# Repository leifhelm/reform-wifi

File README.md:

# WiFi Adapter for MNT Reform

This module is **untested**.

This adapter uses the PCIe and USB interfaces of the RCORE module, like the Pocket Reform.

The schematic is largely from [pocket-reform-wifi](https://source.mnt.re/reform/pocket-reform/-/tree/2fd691b93a8a8b05e923d17600f8ea777f0ab824/pocket-reform-wifi).

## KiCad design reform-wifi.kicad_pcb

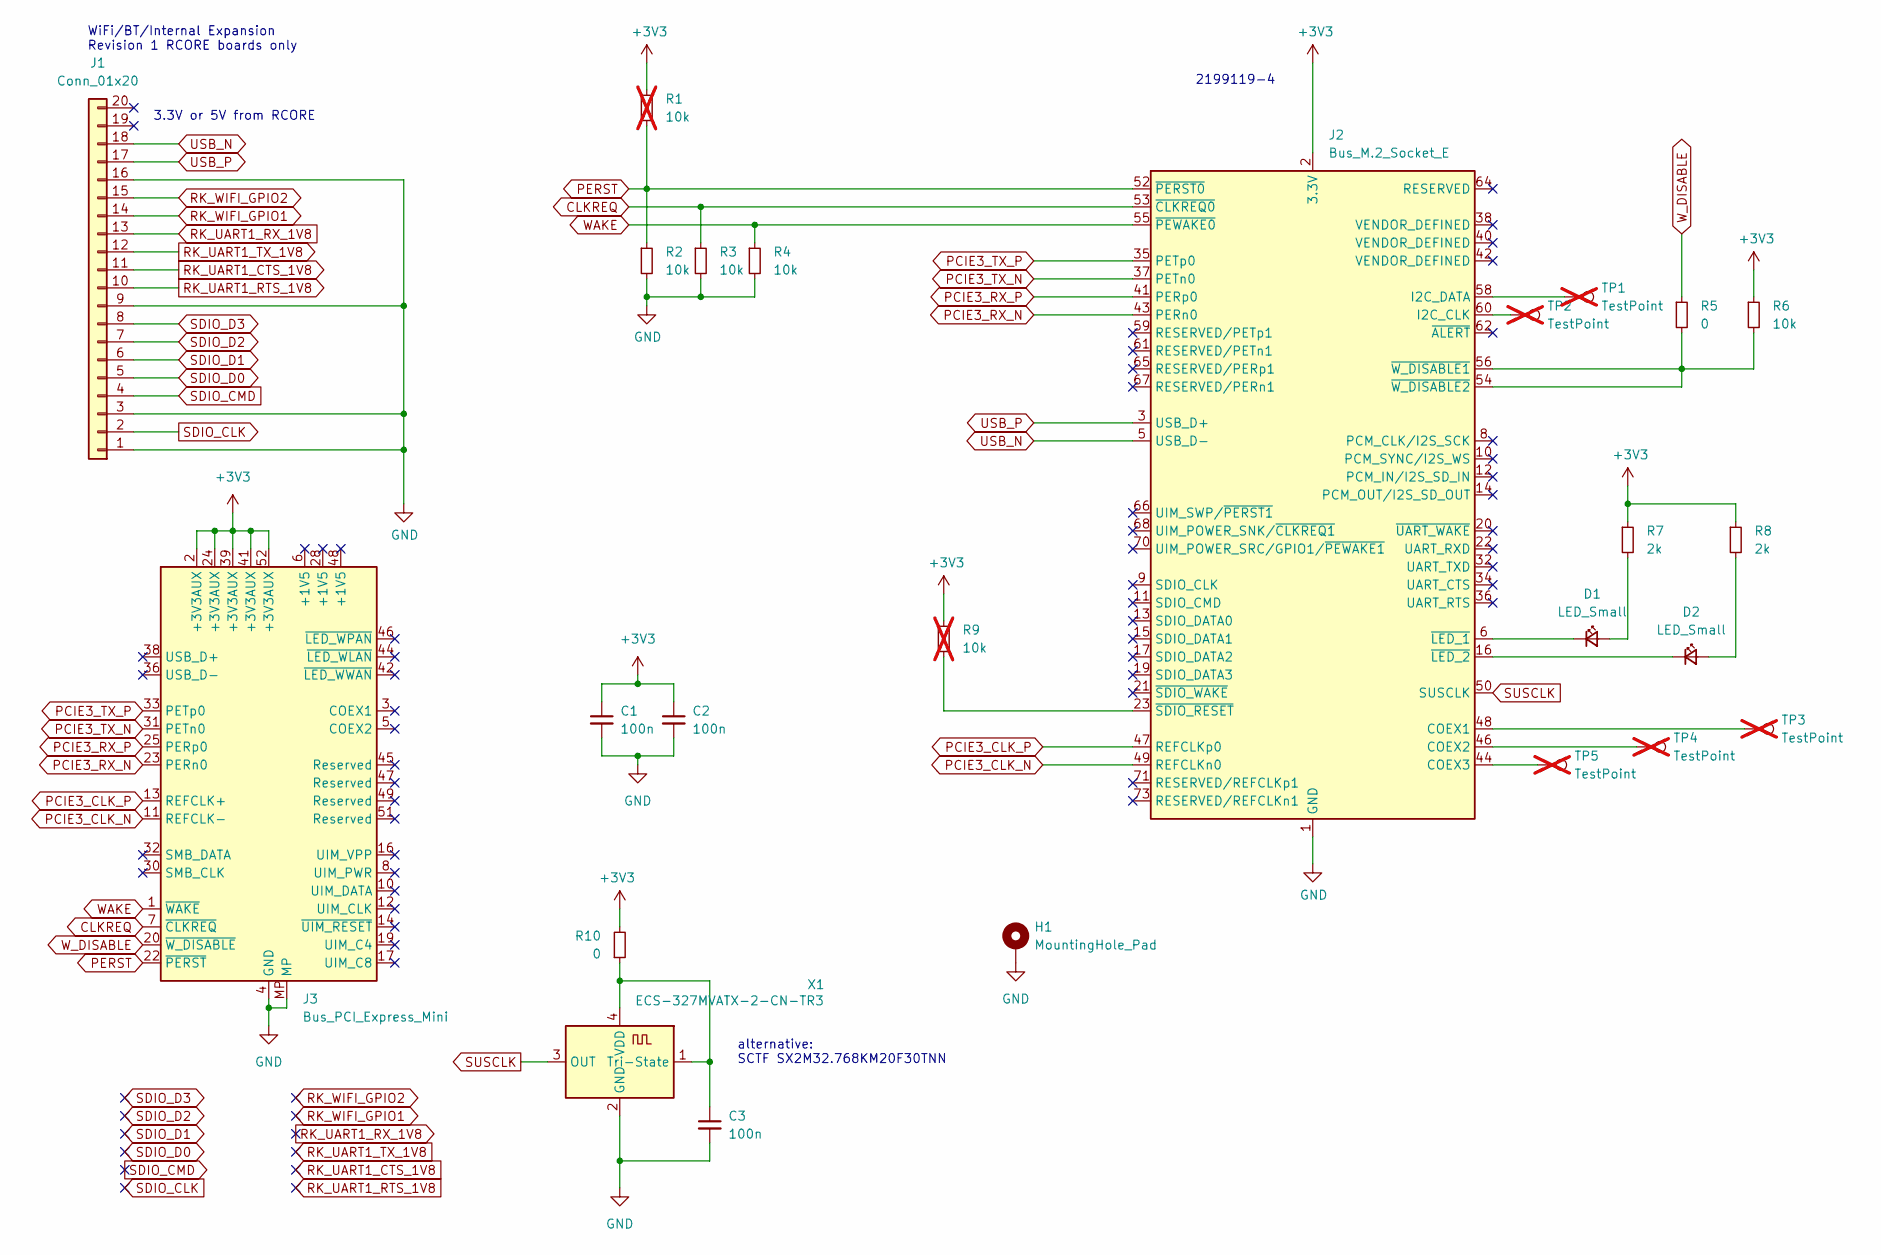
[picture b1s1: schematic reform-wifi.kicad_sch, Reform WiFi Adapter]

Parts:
C1, C2, C3: 100n; C_0603_1608Metric; LCSC C77058
D1, D2: LED_Small; LED_0603_1608Metric; LCSC C5875723
H1: MountingHole_Pad; M.2 Mounting; LCSC C2916320
J1: Conn_01x20; Hirose_FH12-20S-0.5SH_1x20-1MP_P0.50mm_Horizontal; LCSC C596730
J2: Bus_M.2_Socket_E; TE_2199119-4; LCSC C5163551
J3: Bus_PCI_Express_Mini; BUS_PCI_Express_Mini_Full_Card
R1, R9: 10k; R_0603_1608Metric; LCSC C98220; not fitted
R2, R3, R4, R6: 10k; R_0603_1608Metric; LCSC C98220
R5, R10: 0; R_0603_1608Metric; LCSC C95177
R7, R8: 2k; R_0603_1608Metric; LCSC C105576
TP1, TP2, TP3, TP4, TP5: TestPoint; TestPoint_Pad_D1.0mm; not fitted
X1: ECS-327MVATX-2-CN-TR3; Oscillator_SMD_ECS_2520MV-xxx-xx-4Pin_2.5x2.0mm; LCSC C2901603

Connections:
+3V3: C1.1, C2.1, J2.2 (3.3V), J2.4 (3.3V), J2.72 (3.3V), J2.74 (3.3V), J3.2 (+3V3AUX), J3.24 (+3V3AUX), J3.39 (+3V3AUX), J3.41 (+3V3AUX), J3.52 (+3V3AUX), R1.1, R6.1, R7.1, R8.1, R9.1, R10.2
CLKREQ: J2.53 (~CLKREQ0), J3.7 (~CLKREQ), R3.1
GND: C1.2, C2.2, C3.2, H1.1, J1.1, J1.3, J1.9, J1.16, J2.1 (GND), J2.7 (GND), J2.18 (GND), J2.33 (GND), J2.39 (GND), J2.45 (GND), J2.51 (GND), J2.57 (GND), J2.63 (GND), J2.69 (GND), J2.75 (GND), J3.4 (GND), J3.9 (GND), J3.15 (GND), J3.18 (GND), J3.21 (GND), J3.26 (GND), J3.27 (GND), J3.29 (GND), J3.34 (GND), J3.35 (GND), J3.37 (GND), J3.40 (GND), J3.43 (GND), J3.50 (GND), J3.MP, R2.2, R3.2, R4.2, X1.2 (GND)
unnamed: D1.2 (A), R7.2
unnamed: D1.1 (K), J2.6 (~LED_1)
unnamed: D2.2 (A), R8.2
unnamed: D2.1 (K), J2.16 (~LED_2)
unnamed: J2.48 (COEX1), TP3.1
unnamed: J2.46 (COEX2), TP4.1
unnamed: J2.44 (COEX3), TP5.1
unnamed: J2.60 (I2C_CLK), TP2.1
unnamed: J2.58 (I2C_DATA), TP1.1
unnamed: J2.23 (~SDIO_RESET), R9.2
unnamed: J2.54 (~W_DISABLE2), J2.56 (~W_DISABLE1), R5.2, R6.2
unnamed: C3.1, R10.1, X1.1 (Tri-State), X1.4 (VDD)
PCIE3_CLK_N: J2.49 (REFCLKn0), J3.11 (REFCLK-)
PCIE3_CLK_P: J2.47 (REFCLKp0), J3.13 (REFCLK+)
PCIE3_RX_N: J2.43 (PERn0), J3.23 (PERn0)
PCIE3_RX_P: J2.41 (PERp0), J3.25 (PERp0)
PCIE3_TX_N: J2.37 (PETn0), J3.31 (PETn0)
PCIE3_TX_P: J2.35 (PETp0), J3.33 (PETp0)
PERST: J2.52 (~PERST0), J3.22 (~PERST), R1.2, R2.1
RK_UART1_CTS_1V8: J1.11
RK_UART1_RTS_1V8: J1.10
RK_UART1_RX_1V8: J1.13
RK_UART1_TX_1V8: J1.12
RK_WIFI_GPIO1: J1.14
RK_WIFI_GPIO2: J1.15
SDIO_CLK: J1.2
SDIO_CMD: J1.4
SDIO_D0: J1.5
SDIO_D1: J1.6
SDIO_D2: J1.7
SDIO_D3: J1.8
SUSCLK: J2.50 (SUSCLK), X1.3 (OUT)
USB_N: J1.18, J2.5 (USB_D-)
USB_P: J1.17, J2.3 (USB_D+)
WAKE: J2.55 (~PEWAKE0), J3.1 (~WAKE), R4.1
W_DISABLE: J3.20 (~W_DISABLE), R5.1

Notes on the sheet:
2199119-4
alternative: SCTF SX2M32.768KM20F30TNN
3.3V or 5V from RCORE
WiFi/BT/Internal Expansion Revision 1 RCORE boards only

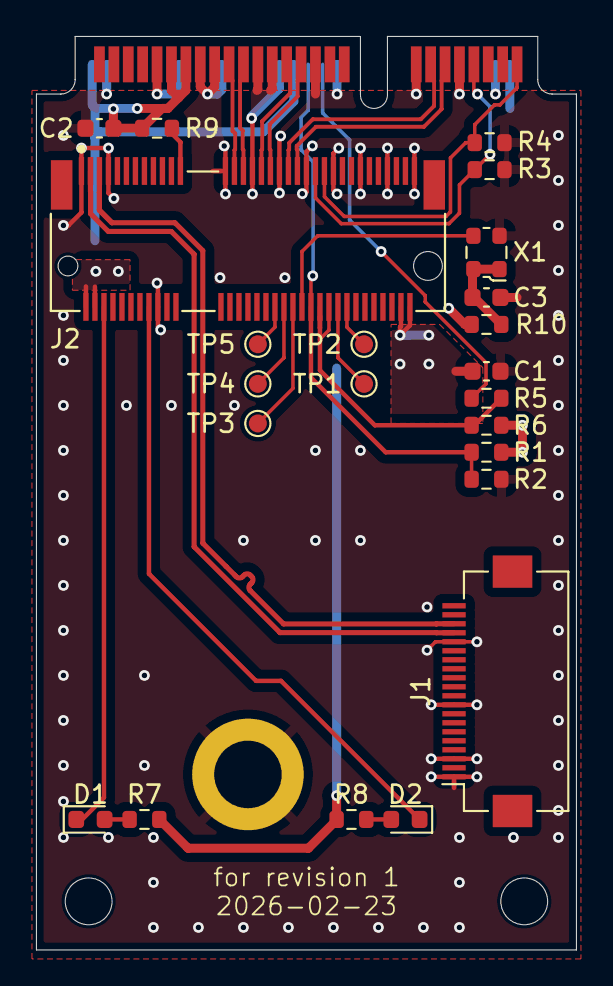
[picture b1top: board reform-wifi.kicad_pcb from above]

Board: 4 copper layers, 30.0 x 50.8 mm, 25 parts (0 on the bottom side), 27 nets.

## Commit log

2026-01-07 Init
2026-02-19 reannotate schematic
2026-02-19 shrink board a little
2026-03-13 update for revision 1
